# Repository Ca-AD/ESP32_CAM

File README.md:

# ESP32_CAM
esp32-CameraWebServer  是基于 Arduino 开发的，可以拿来当做参考  

原理图

PCB

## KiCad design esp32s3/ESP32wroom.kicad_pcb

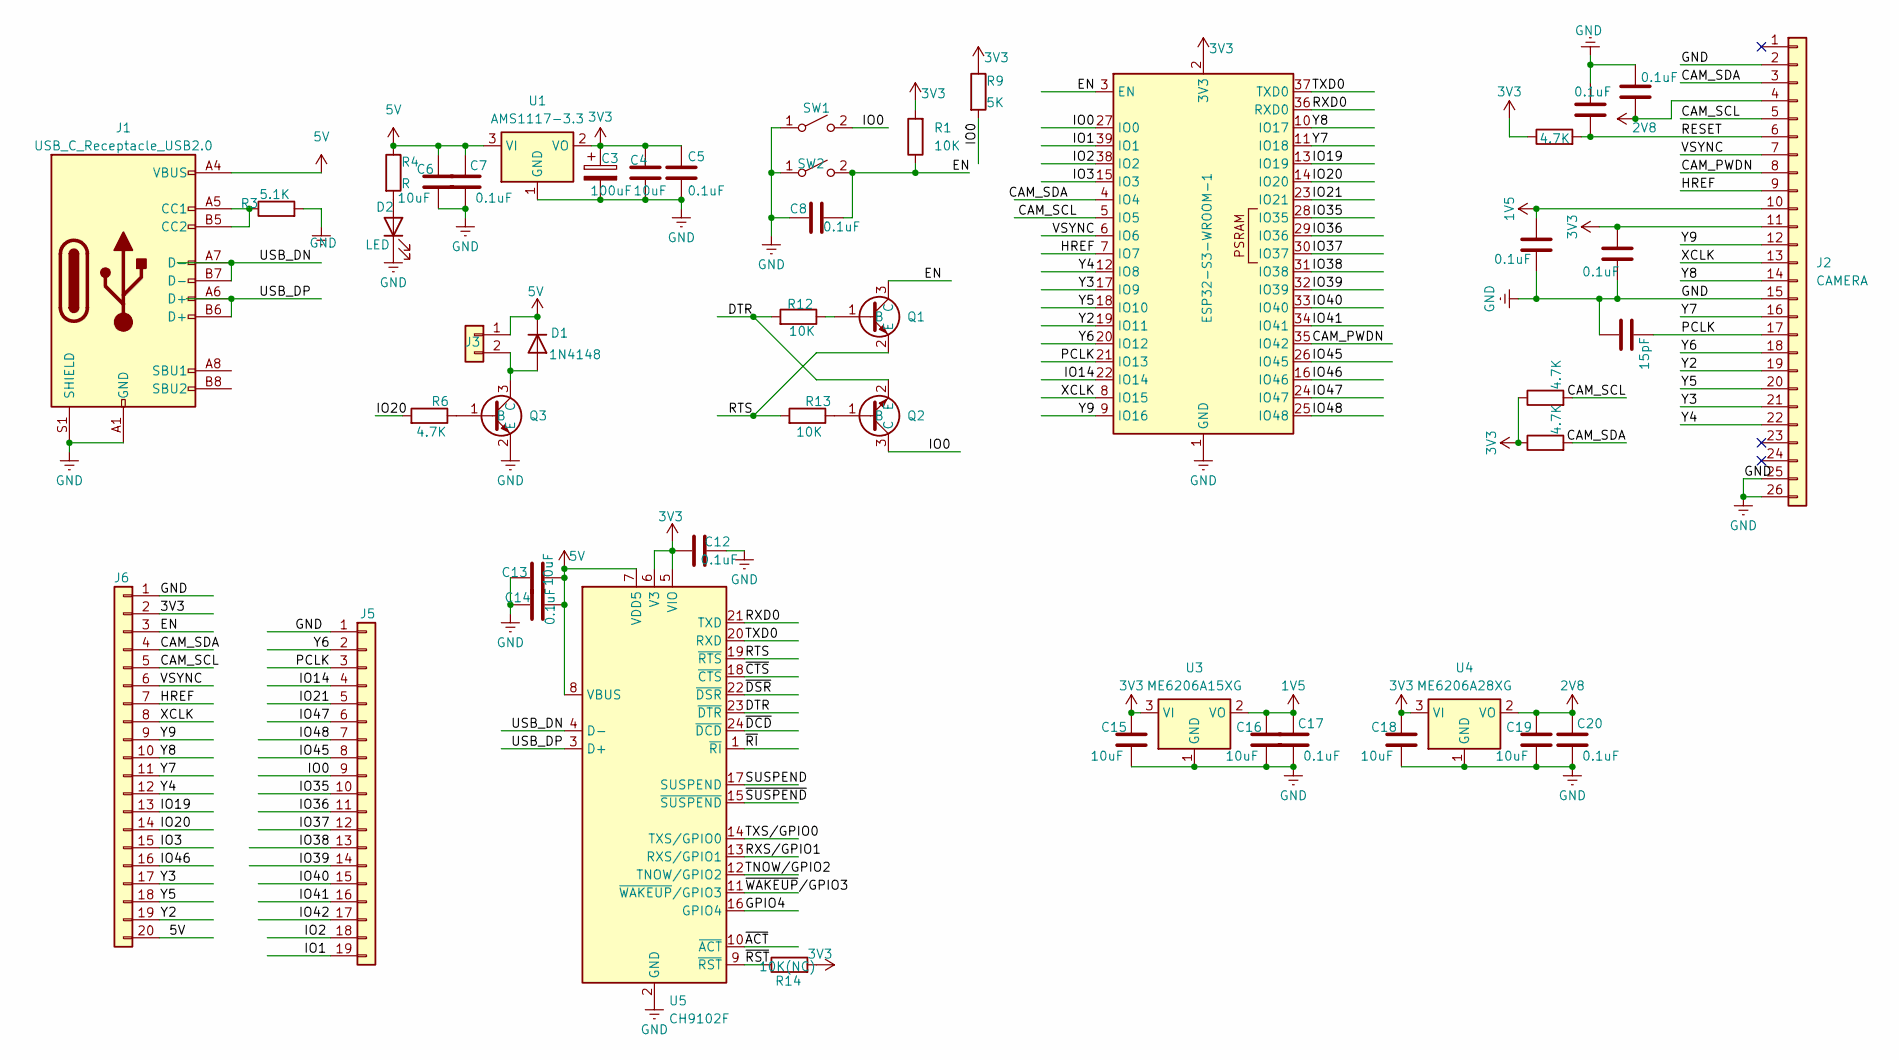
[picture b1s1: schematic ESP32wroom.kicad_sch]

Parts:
C1, C2, C5, C7, C8, C9, C10, C12, C14, C17, C20: 0.1uF; C_0603_1608Metric
C3: 100u_CASE-B-3528_TAJB107K006RNJ; C_1206_3216Metric; Rating 6.3V; Tolerance 10%; MPN TAJB107K006RNJ
C4, C6, C13, C15, C16, C18, C19: 10uF; C_0603_1608Metric
C11: 15pF; C_0603_1608Metric
D1: 1N4148; D_DO-35_SOD27_P7.62mm_Horizontal
D2: LED; LED_0603_1608Metric
J1: USB_C_Receptacle_USB2.0; USB_C_Receptacle_HRO_TYPE-C-31-M-12
J2: CAMERA; Hirose_FH12-24S-0.5SH_1x24-1MP_P0.50mm_Horizontal
J3: Conn_01x02; JST_ACH_BM02B-ACHSS-GAN-ETF_1x02-1MP_P1.20mm_Vertical
J5: Conn_01x19; PinSocket_1x19_P2.54mm_Vertical
J6: Conn_01x20; PinSocket_1x20_P2.54mm_Vertical
Q1, Q2, Q3: SC-59
R1, R12, R13: 10K; R_0603_1608Metric
R2, R6, R10, R11: 4.7K; R_0603_1608Metric
R3: 5.1K; C_0603_1608Metric
R4: R; R_0603_1608Metric
R9: 5K; R_0603_1608Metric
R14: 10K(NC); R_0603_1608Metric
SW1, SW2: SW_SPST; SW_SPST_B3U-1000P
U1: AMS1117-3.3; SOT-223-3_TabPin2
U2: ESP32-S3-WROOM-1
U3: ME6206A15XG; SC-59
U4: ME6206A28XG; SC-59
U5: CH9102F; QFN-24-1EP_4x4mm_P0.5mm_EP2.6x2.6mm

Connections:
1V5: C9.1, C16.2, C17.1, J2.10, U3.2 (VO)
2V8: C1.1, C19.2, C20.1, J2.4, U4.2 (VO)
3V3: C3.1, C4.1, C5.1, C10.1, C12.1, C15.2, C18.2, J2.11, J6.2, R1.2, R2.1, R9.1, R10.1, R11.1, R14.2, U1.2 (VO), U2.2 (3V3), U3.3 (VI), U4.3 (VI), U5.5 (VIO), U5.6 (V3)
5V: C6.2, C7.1, C13.2, C14.2, D1.1 (K), J1.A4 (VBUS), J1.A9 (VBUS), J1.B4 (VBUS), J1.B9 (VBUS), J3.1, J6.20, R4.1, U1.3 (VI), U5.7 (VDD5), U5.8 (VBUS)
/CAM_SCL: J2.5, J6.5, R11.2, U2.5 (IO5)
/CAM_SDA: J2.3, J6.4, R10.2, U2.4 (IO4)
/DTR: Q2.2 (E), R12.2, U5.23 (~DTR)
/EN: C8.2, J6.3, Q1.3 (C), R1.1, SW2.2 (B), U2.3 (EN)
/GPIO4: U5.16 (GPIO4)
/HREF: J2.9, J6.7, U2.7 (IO7)
/IO0: J5.9, Q2.3 (C), R9.2, SW1.2 (B), U2.27 (IO0)
/IO1: J5.19, U2.39 (IO1)
/IO2: J5.18, U2.38 (IO2)
/IO3: J6.15, U2.15 (IO3)
/IO14: J5.4, U2.22 (IO14)
/IO19: J6.13, U2.13 (IO19)
/IO20: J6.14, R6.2, U2.14 (IO20)
/IO21: J5.5, U2.23 (IO21)
/IO35: J5.10, U2.28 (IO35)
/IO36: J5.11, U2.29 (IO36)
/IO37: J5.12, U2.30 (IO37)
/IO38: J5.13, U2.31 (IO38)
/IO39: J5.14, U2.32 (IO39)
/IO40: J5.15, U2.33 (IO40)
/IO41: J5.16, U2.34 (IO41)
/IO45: J5.8, U2.26 (IO45)
/IO46: J6.16, U2.16 (IO46)
/IO47: J5.6, U2.24 (IO47)
/IO48: J5.7, U2.25 (IO48)
/PCLK: C11.2, J2.17, J5.3, U2.21 (IO13)
/RESET: C2.1, J2.6, R2.2
/RTS: Q1.2 (E), R13.2, U5.19 (~RTS)
/RXD0: U2.36 (RXD0), U5.21 (TXD)
/RXS/GPIO1: U5.13 (RXS/GPIO1)
/SUSPEND: U5.17 (SUSPEND)
/TNOW/GPIO2: U5.12 (TNOW/GPIO2)
/TXD0: U2.37 (TXD0), U5.20 (RXD)
/TXS/GPIO0: U5.14 (TXS/GPIO0)
/USB_DN: J1.A7 (D-), J1.B7 (D-), U5.4 (D-)
/USB_DP: J1.A6 (D+), J1.B6 (D+), U5.3 (D+)
/VSYNC: J2.7, J6.6, U2.6 (IO6)
/XCLK: J2.13, J6.8, U2.8 (IO15)
/Y2: J2.19, J6.19, U2.19 (IO11)
/Y3: J2.21, J6.17, U2.17 (IO9)
/Y4: J2.22, J6.12, U2.12 (IO8)
/Y5: J2.20, J6.18, U2.18 (IO10)
/Y6: J2.18, J5.2, U2.20 (IO12)
/Y7: J2.16, J6.11, U2.11 (IO18)
/Y8: J2.14, J6.10, U2.10 (IO17)
/Y9: J2.12, J6.9, U2.9 (IO16)
/~ACT: U5.10 (~ACT)
/~CTS: U5.18 (~CTS)
/~DCD: U5.24 (~DCD)
/~DSR: U5.22 (~DSR)
/~RI: U5.1 (~RI)
/~RST: R14.1, U5.9 (~RST)
/~SUSPEND: U5.15 (~SUSPEND)
/~WAKEUP/GPIO3: U5.11 (~WAKEUP/GPIO3)
GND: C1.2, C2.2, C3.2, C4.2, C5.2, C6.1, C7.2, C8.1, C9.2, C10.2, C11.1, C12.2, C13.1, C14.1, C15.1, C16.1, C17.2, C18.1, C19.1, C20.2, D2.1 (K), J1.A1 (GND), J1.A12 (GND), J1.B1 (GND), J1.B12 (GND), J1.S1 (SHIELD), J2.2, J2.15, J2.25, J2.26, J5.1, J6.1, Q3.2 (E), R3.2, SW1.1 (A), SW2.1 (A), U1.1 (GND), U2.1 (GND), U2.40 (GND), U2.41 (GND), U3.1 (GND), U4.1 (GND), U5.2 (GND), U5.25 (GND); also elsewhere on the board
unnamed: D1.2 (A), J3.2, Q3.3 (C)
unnamed: D2.2 (A), R4.2
unnamed: J1.A5 (CC1), J1.B5 (CC2), R3.1
unnamed: Q1.1 (B), R12.1
unnamed: Q2.1 (B), R13.1
unnamed: Q3.1 (B), R6.1

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
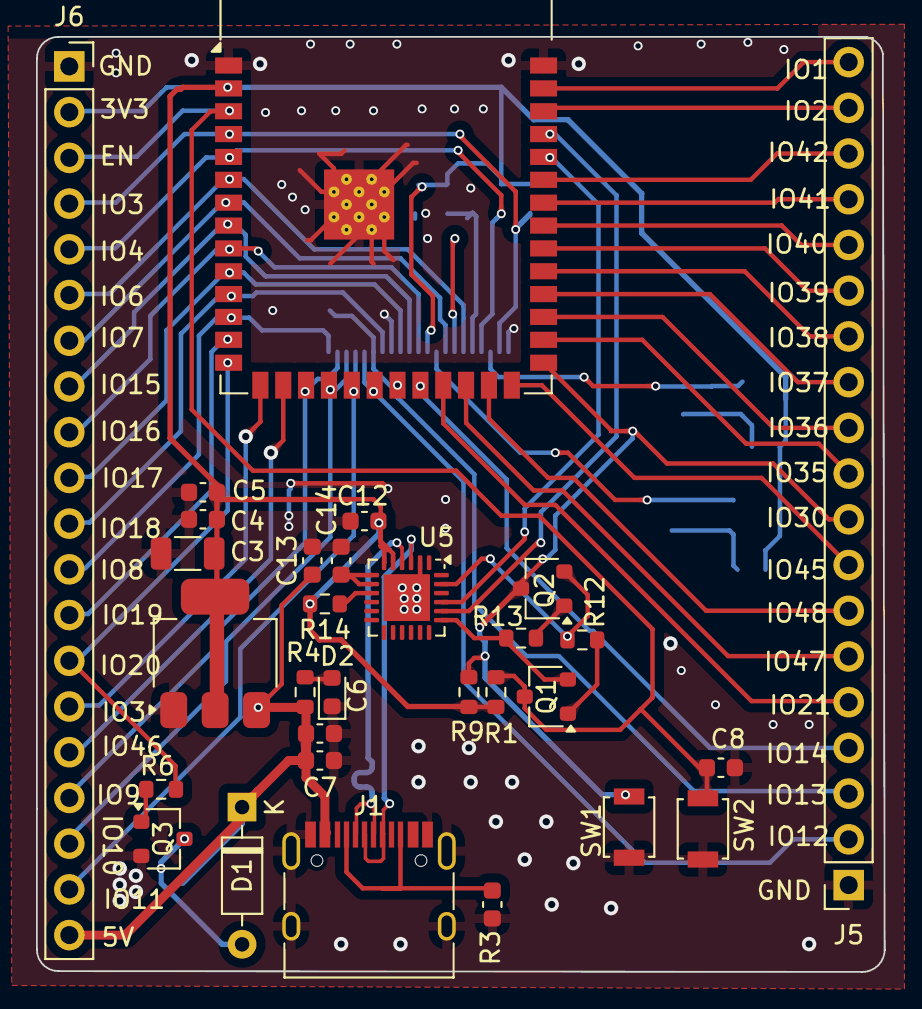
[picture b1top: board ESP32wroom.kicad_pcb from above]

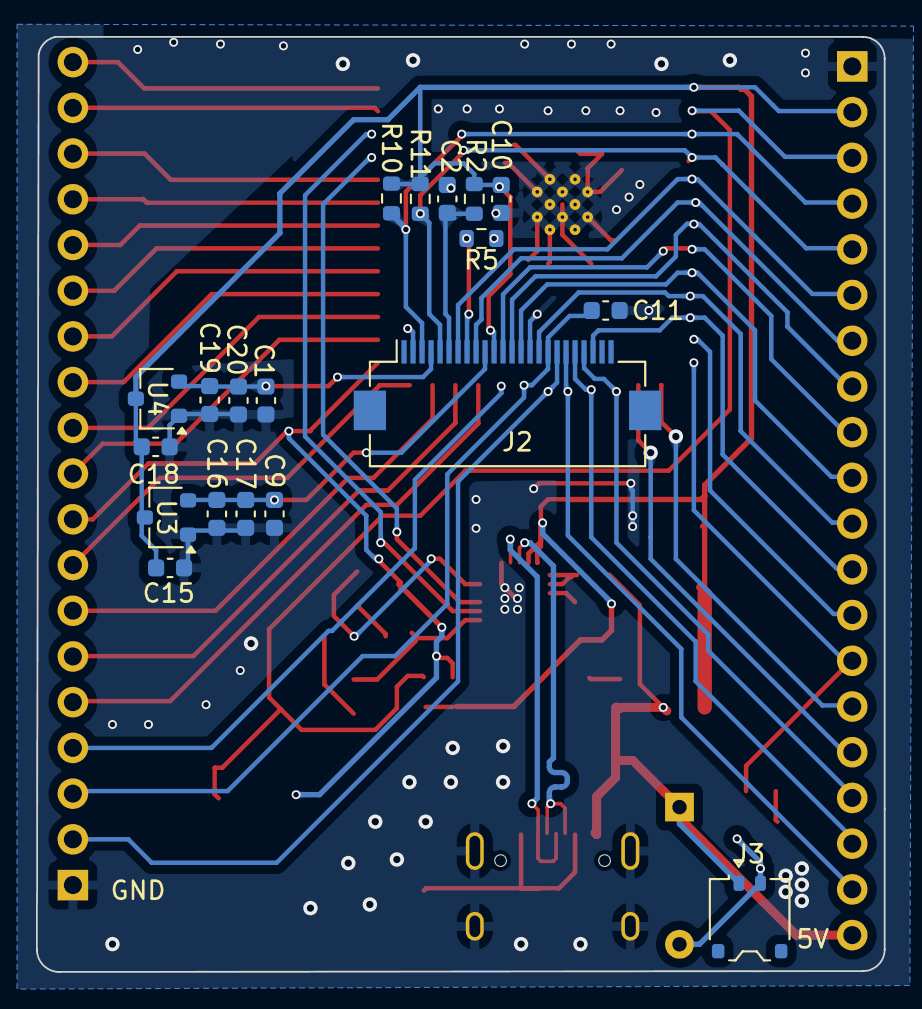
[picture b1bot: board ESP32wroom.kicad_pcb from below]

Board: 2 copper layers, 47.1 x 51.9 mm, 49 parts (19 on the bottom side), 55 nets.

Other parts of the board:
R5: 1K; R_0603_1608Metric

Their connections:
GND: R5.2; also elsewhere on the board

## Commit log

2025-03-13 ESP32s3
2025-03-13 添加图片
2025-03-13 图片路径
